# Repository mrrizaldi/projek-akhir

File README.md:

# Proyek Akhir — Sistem Monitoring Detak Jantung Kontinu (IoT Edge Computing)

Monorepo Proyek Akhir untuk pemantauan EKG kontinu dengan klasifikasi aritmia
**di edge**. Sinyal EKG satu lead diakuisisi AD8232, diproses dan diklasifikasi
oleh model TinyML INT8 di ESP32-S3, lalu hasil per detak dipublikasikan lewat
MQTT ke ThingsBoard. Klasifikasi berjalan di alat, bukan di server.

## Struktur

| Subdir | Isi | Toolchain |
|---|---|---|
| `model/` | Jalur TinyML: data MIT-BIH → preprocessing → pelatihan → kuantisasi INT8 → ekspor | Python 3.11 + TensorFlow/TFLite |
| `firmware/` | Program ESP32-S3: akuisisi 360 Hz, deteksi R-peak, inferensi TFLite Micro, MQTT | PlatformIO (C/C++) |
| `dashboard/` | ThingsBoard CE (broker MQTT, rule engine, dashboard) dan skrip pengukuran pipeline | Docker Compose, Python |
| `hardware/` | PCB mainboard rev2: skematik, layout, library DevKitC-1, pemeriksaan otomatis ([`hardware/mainboard/`](hardware/mainboard/README.md)) | KiCad 9 |
| `laporan/` | Dokumen LaTeX: `proposal-pa`, `buku-pa`, `surat-magang`, `shared` | pdflatex + bibtex |
| `scripts/` | Otomasi lintas-komponen (sinkronisasi artefak) | bash |
| `docs/` | Pola penulisan laporan PA dan arsip rencana kerja | Markdown |

## Alur artefak (produsen → konsumen)

- `model/` menghasilkan `model_int8.h` → dikonsumsi `firmware/include/`.
- `model/scripts/export_golden.py` menghasilkan `firmware/test/golden_ref.h`
  (regression test C ↔ Python).
- `model/artifacts/metrics/` (plot eksperimen) dan `dashboard/preview.png`
  menghasilkan figure → dikonsumsi `laporan/*/gambar/`. Diagram ilustrasi
  digambar penulis langsung ke `laporan/*/gambar/`.
- Sinkronisasi lewat `scripts/export_artifacts.sh`. Artefak tidak disalin manual.

Kebijakan commit: figure final dan header `.h` hasil generate **di-commit**,
sehingga laporan dan firmware dapat di-build tanpa menjalankan seluruh pipeline
model. Data mentah MIT-BIH dan berkas intermediate (`.npz`) **di-ignore**
(lihat `.gitignore`).

## Build cepat

```bash
# Laporan (ukuran kertas tetap per projek)
cd laporan/buku-pa && make pdf            # -> output/main.pdf
# Model
cd model && make train && make quantize && make export
# Firmware
cd firmware && pio run -e esp32-s3 -t upload && pio device monitor
cd firmware && pio test -e native         # uji di PC, tanpa board
# Dashboard
cd dashboard && docker compose up -d      # -> http://localhost:8080
```

## Status komponen

| Komponen | Kondisi | Bukti |
|---|---|---|
| `model/` Fase 0-8 | Selesai | `make poc` 8/8, INT8 22,94 KB, DS2 F1 0,6594, AUC 0,9334 |
| `model/` ablasi Fase A-G | Selesai, konfigurasi tidak berubah | 10 usul × 3-6 seed; TEST-B/C 85.812 beat / 39 pasien ([peta](model/docs/README.md)) |
| `firmware/` env `esp32-s3` | Berjalan di board | Inferensi 26,6 ms/detak, tensor arena 12.948 B, sampel hilang 0; MQTT PDSR 99,2-100%, latensi median 939-1.108 ms |
| Akuisisi sinyal tubuh | Selesai: data resmi = sesi 22 Okt 2026 siang (R1–R4, 927,1 s, 4/4 Berhasil) | Indeks sesi di [`model/data/recordings/README.md`](model/data/recordings/README.md); rekaman pengembangan diarsipkan di [`model/data/arsip/rekaman-uji-coba/`](model/data/arsip/rekaman-uji-coba/README.md) |
| `firmware/` test perangkat | Lulus di board | `pio test -e esp32-s3`: 29 test (preprocessing, inferensi, buzzer, TFT, ADC, INA219, tombol, integrasi replay) |
| `firmware/` env `native` | Lulus | `pio test -e native`: 23 test |
| `dashboard/` | Berjalan | ThingsBoard CE self-host, dashboard tujuh widget, uji deduplikasi |
| `laporan/proposal-pa` | Lengkap | Bab 1-3 dan abstrak |
| `laporan/buku-pa` | Draf Bab 1-5 | Gambar ilustrasi berupa placeholder (`grep -rn PLACEHOLDER-GAMBAR laporan/`); angka konsumsi daya menunggu pengukuran (`grep -rn PLACEHOLDER-DATA laporan/buku-pa`) |

Status rinci per fase model berada di `model/CLAUDE.md`. Berkas ini hanya peta,
agar tidak ada dua sumber kebenaran. Pekerjaan yang masih terbuka (konsumsi
daya, WiFi OFF darurat, rekaman ke server, PCB rev2) didaftar bertanggal di
[`model/CLAUDE.md` §Pekerjaan terbuka](model/CLAUDE.md#pekerjaan-terbuka).

## Peta dokumentasi

| Dokumen | Isi |
|---|---|
| [`CLAUDE.md`](CLAUDE.md) | Aturan kerja repo, gate point, kebijakan gambar |
| [`model/README.md`](model/README.md) | Ringkasan komponen model |
| [`model/docs/README.md`](model/docs/README.md) | Peta walkthrough Fase 0-8 dan HW, angka rujukan, eksperimen yang tidak diadopsi |
| [`model/docs/arsip/README.md`](model/docs/arsip/README.md) | Indeks arsip desain, rencana, dan changelog eksperimen model/hardware |
| [`firmware/README.md`](firmware/README.md) | Env PlatformIO, perintah, pin map, perintah serial |
| [`dashboard/README.md`](dashboard/README.md) | ThingsBoard, kontrak payload, pengukuran pipeline |
| [`.claude/skills/`](.claude/skills/) | Skill penulisan laporan (`struktur-pa`, `narasi-pa`, `tabel-pa`, `buku-ikut-proposal`) dan firmware |
| [`docs/arsip/README.md`](docs/arsip/README.md) | Indeks arsip rencana kerja laporan |
| [`scripts/README.md`](scripts/README.md) | Otomasi lintas-komponen (sinkronisasi artefak) |
| [`model/docs/arsip/2026-10-08-pcb-rev2-adjustment.md`](model/docs/arsip/2026-10-08-pcb-rev2-adjustment.md) | Penyesuaian PCB rev1 → rev2 (skematik KiCad di luar repo) |
| `laporan/CLAUDE.md` | Aturan gaya penulisan laporan |
| `model/PRD_Model_Aritmia_TinyML.pdf` | Spesifikasi resmi jalur model |

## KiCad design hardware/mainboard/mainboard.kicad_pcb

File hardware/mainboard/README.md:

# Mainboard (PCB rev2)

Proyek KiCad untuk papan induk alat: ESP32-S3-DevKitC-1 N16R8, AD8232, TFT
ST7789 1,47", INA219, modul buzzer pasif, tiga tombol, dan jalur catu
baterai 18650 (TP4056 + boost MT3608) dengan saklar on-off. Semua modul
dipasang lewat header 2,54 mm. Papan dua lapis, 110 × 103 mm.

Kondisi: skematik dan layout lengkap, pemeriksaan otomatis lulus (lihat
**Pemeriksaan**). Belum difabrikasi, dan butir di **Yang belum terverifikasi**
harus dicek pada modul fisik sebelum Gerber dikirim.

## Berkas

| Berkas | Isi |
|---|---|
| `mainboard.kicad_pro`, `.kicad_sch`, `.kicad_pcb` | proyek KiCad 9.0.2 |
| `lib/PA.kicad_sym`, `lib/PA.pretty/` | simbol dan footprint ESP32-S3-DevKitC-1 (library proyek, dirujuk lewat `${KIPRJMOD}`) |
| `cek_board.py` | pemeriksaan netlist, ERC, DRC, dan paritas skematik–PCB; memanggil `cek_tata_letak.py` |
| `cek_tata_letak.py` | pemeriksaan pcbnew (`/usr/bin/python3`): lebar jalur per netclass, jarak courtyard ≥ 1 mm, teks depan dan belakang |
| `tata_letak.py` | alat layout (`/usr/bin/python3`): posisi terkunci, rute manual, pembersihan sesudah autoroute, pad GND solid, tuang zona, penempat teks, ukiran |

Berkas dibuat dengan KiCad 9.0.2 dan bisa dibuka KiCad 10. Arah sebaliknya
tidak bisa: berkas KiCad 10 (misalnya skematik rev2 yang disusun dengan
KiCad 10.0.6) ditolak KiCad 9 dengan pesan `Failed to load schematic`.

## Peta pin

Sama dengan `firmware/include/perangkat.h`. Nomor pad U1 mengikuti footprint
resmi Espressif: pad 1–22 kolom kiri dari atas (3V3 … GND), pad 23–44 kolom
kanan dari bawah (GND … GND). Urutan fisik kedua kolom sudah dicocokkan 44/44
dengan gambar pinout resmi ESP32-S3-DevKitC-1.

| Fungsi | GPIO | Pad U1 | Net | Tujuan |
|---|---|---|---|---|
| EKG OUT / LO− / LO+ | 1 / 2 / 42 | 41 / 40 / 39 | `ECG_OUT` / `ECG_LON` / `ECG_LOP` | J3 pin 3 / 4 / 5 |
| TFT SCK / MOSI | 9 / 8 | 15 / 12 | `TFT_SCK` / `TFT_MOSI` | J2 pin 3 / 4 |
| TFT RES / DC | 10 / 11 | 16 / 17 | `TFT_RST` / `TFT_DC` | J2 pin 5 / 6 |
| Buzzer | 13 | 19 | `BUZZ` | J9 pin 2 |
| Tombol 1 / 2 / 3 | 4 / 5 / 6 | 4 / 5 / 6 | `BTN1..3` | SW1..3 ke GND |
| INA219 SDA / SCL | 17 / 18 | 10 / 11 | `I2C_SDA` / `I2C_SCL` | U2 pin 4 / 3 |
| 3V3 | – | 1, 2 | `+3V3` | semua VCC modul, SDN AD8232, BLK TFT |
| 5V | – | 21 | `+5V` | keluaran D2 |
| GND | – | 22, 23, 24, 44 | `GND` | semua pin GND DevKit tersambung |

Urutan pin header modul:

| Ref | Modul | Pin 1 → n |
|---|---|---|
| J3 | AD8232 | GND, 3V3, OUT, LO−, LO+, SDN |
| J2 | TFT ST7789 | GND, VCC, SCL, SDA, RES, DC, CS, BLK (CS ke GND, BLK ke 3V3) |
| U2 | INA219 | VCC, GND, SCL, SDA, VIN−, VIN+ |
| J9 | buzzer A18009 | GND, I/O, VCC |
| J1 | boost MT3608 | VIN+, VIN−, VOUT+, VOUT− |
| J10 | saklar on-off berlampu (di casing) | masuk (VSYS), keluar ke boost (VSW), GND lampu |
| J4 / J5 / J6 | TP4056 | IN+ IN− / B+ B− / OUT+ OUT− |
| J8 | kabel holder 18650 (JST PH) | +, − |

## Catu daya

```
 J8 baterai ── J5 B+/B− (TP4056) ── J6 OUT+ = VBAT_OUT ── U2 VIN+ ─shunt─ VIN− = VBAT_SENSE
                                                                             │
                     J4 IN+ = VCHG ──┬── gate Q1 (R1 10k ke GND)             D
                                     │                                   Q1 AO3401A
                                     └── D1 SS34 ──► VSYS ◄──────────────── S
                                                      │
                                              J10 saklar on-off
                                                      │ VSW
                                     J1 VIN+ ◄────────┘    J1 VOUT+ = VBOOST ── D2 SS34 ──► +5V ── U1 pin 5V, C1 47 µF, C2 100 nF
```

- Tanpa charger: gate Q1 ditarik R1 ke GND, Q1 menyala, baterai mencatu boost.
- Dengan charger: VCHG 5 V mematikan Q1, sehingga baterai hanya menerima arus
  isi dari TP4056 dan tidak mencatu beban. Boost dicatu dari VCHG lewat D1.
  Katoda D1 ada di VSYS (masukan boost), bukan di +5V. Kalau katoda D1 di +5V,
  body diode Q1 tetap mengalirkan baterai ke boost dan sel terkuras selama
  dicas.
- Saklar J10 memutus VSYS sebelum boost. OFF berarti alat mati total, juga
  saat charger tercolok, sedangkan pengisian baterai tetap berjalan karena
  TP4056 ada di depan saklar. Lampu saklar dicatu dari VSYS (±3,0–4,6 V).
- R2 1 MΩ (R_Dummy di skematik rev2) dipertahankan apa adanya: beban ±4 µA
  dari VBAT_SENSE ke GND.

## Layout

| Area | Isi | Alasan |
|---|---|---|
| Tengah | U1, USB menghadap tepi bawah | semua GPIO terpakai ada di kolom kiri kecuali EKG |
| Kanan atas | J3 AD8232, C4 | pad 39–41 U1 sejajar J3 pin 3–5, jalur EKG lurus 9 mm |
| Kanan bawah | jalur baterai, INA219, Q1, D1, D2, header TP4056/boost/baterai | jauh dari AD8232; modul boost di luar papan lewat kabel |
| Kiri | TFT, buzzer; tombol SW1–SW3 berjajar tegak di tepi kiri (x 53–57,5, y 57,5–88) | SPI TFT berlawanan sisi dengan jalur analog; tombol mudah dijangkau dari sisi papan |
| Atas U1 | rule area `antena_devkit` | tanpa tembaga dan via di bawah antena WROOM |
| Bawah | rule area `holder_18650` 80 × 24 mm (x 66–146, y 116,5–140,5) + garis silkscreen | tempat holder 18650 berkabel yang ditempel; baterai 65 × 18 mm, holder ±77 × 21 mm, margin 1,5 mm tiap sisi; footprint dilarang, jalur dan GND pour boleh |

Jalur yang dirute manual dan dikunci (`locked`): tiga jalur EKG (F.Cu),
catu AD8232 (3V3 dari pad 2 U1 lewat B.Cu ke C4/J3 pin 2, SDN ke 3V3),
I2C ke INA219 (SDA di F.Cu; SCL turun lewat via ke B.Cu di x 118 dan
menyeberang di bawah SDA, karena urutan pin INA219 SCL–SDA terbalik terhadap
urutan dari DevKit), 3V3 ke INA219, 3V3 sisi kiri (U1 pad 2 ke C3), dan
seluruh jalur daya (termasuk cabang gate Q1 dan R2). Gate Q1 lewat B.Cu
karena urutan pin SOT-23 (G, D, S searah jarum jam) berlawanan dengan arah
net di sekitarnya, dan gate tidak membawa arus. Sisa sinyal digital dirute
Freerouting 2.3.0. GND dituang di kedua lapis.

Batas JLCPCB untuk 2 lapis 1 oz (halaman *PCB Capabilities*): jalur/clearance
0,10 mm, jalur ke lubang PTH 0,28 mm (rekomendasi 0,35 mm), via lubang 0,15 /
pad 0,25 mm (lubang < 0,3 mm lebih mahal), ring PTH 0,18 mm (rekomendasi
0,25 mm), teks silkscreen tinggi 1,0 mm dan garis 0,15 mm, tembaga ke tepi
0,2 mm. Profil papan ini adalah profil "ideal teknis": lebar mengikuti
kebutuhan arus menurut IPC-2221 (1 oz, kenaikan suhu 10 °C: 0,3 mm ±1 A,
1,0 mm ±2,4 A), jarak dan ring mengikuti rekomendasi JLCPCB.

| Netclass (`mainboard.kicad_pro`) | Net | Lebar | Clearance | Via |
|---|---|---|---|---|
| `Default` | sinyal digital, `+3V3`, GND | 0,3 mm | 0,35 mm | 0,9/0,4 mm |
| `ECG` | `/ECG_*` | 0,4 mm | 0,35 mm | 0,9/0,4 mm |
| `Power` | `/+5V /VBOOST /VSYS /VSW /VCHG /VBAT_OUT /VBAT_SENSE /BAT+ /BAT-` | 1,0 mm | 0,35 mm | 1,2/0,6 mm |

Arus terbesar di papan: jalur baterai/boost ±1 A puncak (MT3608 dibatasi
2 A), sehingga 1,0 mm memberi margin di atas batas boost. Sinyal hanya
membawa miliampere; 0,3 mm dipilih karena tiga kali minimum JLCPCB dan muat di
sela pin DevKit tanpa menyempit (0,3 + 2 × 0,35 = 1,0 mm ≤ celah 1,04 mm).

Jarak antar-courtyard komponen minimal 1,0 mm. Semua pad GND memakai thermal
relief kecuali C2-2, yang disambung penuh (*solid*) karena hanya mendapat satu
spoke di sela antara U1 dan jalur +5V.

Teks: referensi di silkscreen (tinggi ≥ 1,0 mm, batas JLCPCB) dan value di
Fab, sejajar sumbu header dan di sisi yang berlawanan, tanpa menumpuk dan
tidak di atas pad. Pengecualian: ref C4 mendatar di atas C4, karena celah
9 mm antara U1 dan J3 tidak muat teks tegak.

## Perbedaan terhadap skematik rev2

Skematik rev2 (`mainboard.kicad_sch`, KiCad 10.0.6, PCB belum di-layout)
dipakai sebagai acuan rangkaian. Perbedaannya:

| Bagian | Rev2 | Mainboard ini | Alasan |
|---|---|---|---|
| Net 3V3 | label `3.3V` (ESP, AD8232, buzzer) dan simbol `+3.3V` (TFT) | satu net `+3V3` | nama berbeda di KiCad = dua net terpisah; VCC TFT tidak tersambung ke 3V3 ESP |
| Pull-up tombol | R11–R13 1 kΩ ke +5V | dihapus, `INPUT_PULLUP` | GPIO ESP32-S3 maksimum 3,6 V |
| BLK TFT | tidak tersambung | ke 3V3 | backlight selalu menyala |
| Katoda D1 | ke +5V | ke VSYS | baterai tidak terkuras saat dicas |
| Saklar daya | tidak ada | J10 di VSYS | |
| Simbol U1 | ESP32-S3-DEVKITC-1-N8R8 | ESP32-S3-DevKitC-1-N16R8 | papan yang dipakai N16R8 |
| GND DevKit | hanya pin GND kanan atas | keempat pin GND | |
| Header boost | 2 pin (Input, Output) | 4 pin dengan GND | GND modul boost punya jalur sendiri |
| Footprint header J1–J9 | belum diisi | PinSocket/PinHeader 2,54 mm, JST PH untuk baterai | |
| Nama net | `SCL`, `OUT`, `buzz`, dll. | berprefiks (`I2C_`, `TFT_`, `ECG_`) | nama sama otomatis menyatu di KiCad |

Ukuran footprint pasif mengikuti rev2: R dan C 0805 HandSolder, tombol
`SW_PUSH_6mm_H7.3mm`. C1 memakai `CP_Radial_D5.0mm_P2.00mm` (pad sama dengan
rev2) agar tanda polaritas tercetak.

## Footprint ESP32-S3-DevKitC-1

Diambil dari library resmi Espressif (`espressif/kicad-libraries`,
`ESP32-S3-DevKitC.kicad_mod` dan simbol `ESP32-S3-DevKitC`). Posisi pad tidak
diubah: 2 × 22 pin, pitch 2,54 mm, jarak antar-baris 22,86 mm. Yang diubah
hanya lubang dan pad: lubang 0,8 mm menjadi 1,0 mm, pad oval 2,0 mm (mendatar)
× 1,5 mm (tegak), ring 0,25 mm sesuai rekomendasi JLCPCB. Pin header persegi
0,64 mm berdiagonal 0,9 mm, sehingga tidak masuk lubang 0,8 mm; 1,0 mm sama
dengan footprint `PinSocket` KiCad. Pad 1,5 mm tegak menyisakan celah 1,04 mm
antar-pin satu kolom, cukup untuk jalur 0,3 mm + clearance 2 × 0,35 mm. Jalur
3V3 ke AD8232 dan I2C ke INA219 menyeberangi kolom pin lewat celah ini. Simbol diturunkan dari format KiCad 10
ke format KiCad 9 tanpa mengubah pin.

## Pemeriksaan

```bash
python3 hardware/mainboard/cek_board.py
```

Hasil yang diharapkan:

```
netlist: 87/87 pin sesuai peta
+5V di luar jalur daya: tidak ada
ERC: error 0 warning 0
DRC error: 0, unconnected: 0, paritas skematik: 0
lebar jalur: 0 temuan
jarak courtyard: 0 temuan
teks: 0 temuan
LULUS
```

Skrip keluar dengan kode 1 bila satu pin saja menyimpang dari peta di atas,
bila ada jalur lebih tipis dari netclass-nya, dua courtyard berjarak < 1 mm,
atau teks menumpuk, di atas pad, keluar tepi, atau tidak searah header.
Peta pin di skrip (`PIN_U1`, `PIN_LAIN`) wajib diperbarui bersamaan dengan
`perangkat.h` setiap kali pin dipindah.

## Ukiran nama

Silkscreen sisi belakang, dicerminkan agar terbaca dari bawah, di balik area
holder (yang bebas footprint sehingga sisi belakangnya tanpa pad):

| Baris | Teks | Tinggi | Posisi |
|---|---|---|---|
| 1 | Muhammad Rafi Rizaldi | 2,5 mm | (106; 125) |
| 2 | 3123600001 | 2,0 mm | (106; 131) |

Teksnya diatur di `UKIRAN` dan `POSISI_UKIRAN` (`tata_letak.py`).

## Mengubah desain

Perubahan rangkaian:

1. Buka `mainboard.kicad_pro` di KiCad 9 atau lebih baru.
2. Ubah skematik. Penerapan ke board lewat skrip pcbnew (lihat skill
   `kicad-pcb-pa` aturan 5), bukan F8, agar nama net tetap `/NAMA`.

Rute ulang seluruh papan (posisi di `POSISI`, rute manual di fungsi `rute_*`
pada `tata_letak.py`), dijalankan dari `hardware/mainboard/`:

```bash
/usr/bin/python3 tata_letak.py hapus
/usr/bin/python3 tata_letak.py rute
/usr/bin/python3 tata_letak.py tuang
```

Lalu autoroute sisa sinyal dengan Freerouting (server MCP kicad: `open_project`,
`autoroute` dengan `maxPasses` 60), kemudian:

```bash
/usr/bin/python3 tata_letak.py bersih
/usr/bin/python3 tata_letak.py solid
/usr/bin/python3 tata_letak.py teks
/usr/bin/python3 tata_letak.py ukiran
/usr/bin/python3 tata_letak.py tuang
python3 cek_board.py
```

Hasil yang diharapkan: baris terakhir `cek_board.py` adalah `LULUS`.
Freerouting bisa melapor sukses sambil meninggalkan sambungan; bila DRC
melapor `unconnected`, sambungan itu ditambahkan ke fungsi `rute_*` di
`tata_letak.py` lalu seluruh urutan diulang dari `hapus`.

## Yang belum terverifikasi

1. **Jarak antar-baris header DevKit fisik.** Footprint memakai 22,86 mm
   (resmi Espressif). Ukur papan N16R8 yang dipakai, karena klon bisa berbeda.
2. **Urutan pin tiap modul** (J2, J3, U2, J9) terhadap silkscreen modul yang
   dipegang. Urutan pin TFT 1,47" berbeda antar-vendor.
3. **Ruang mekanik modul.** Ukuran dari penjual saling berbeda (AD8232 35×22
   sampai 36×33 mm, TFT 19,5×44,5 atau 22×38,5 mm, INA219 22×20 mm), dan
   outline badan modul belum digambar di PCB. Bila dibaringkan ke arah dalam
   papan, badan TFT menutupi C6 dan badan AD8232 menutupi H2. Komponen SMD di
   bawahnya aman selama modul terangkat di atas female header. Kepala baut H2
   perlu dicek terhadap sisi bawah modul AD8232.
4. **Jalur catu dengan D1 di VSYS** belum diuji di breadboard. Ukur VSYS dan
   +5V dengan charger tercolok dan tercabut, dan pastikan arus baterai ≈ 0
   saat dicas.
5. **Konektor baterai** memakai JST PH 2 mm. Sesuaikan dengan kabel holder
   18650 yang dipakai, dan ukur holdernya: area di papan 80 × 24 mm.
6. **Tegangan lampu saklar J10.** Lampu dicatu VSYS ±3,0–4,6 V. Lampu LED
   12 V atau neon 220 V tidak akan menyala di tegangan ini; cek tulisan di
   badan saklar sebelum memakai pin lampu.

## Ekspor fabrikasi

Berkas untuk JLCPCB dibuat dengan pengaturan dari panduan resmi JLCPCB untuk
KiCad: lapisan F/B.Cu, F/B.Paste, F/B.Silkscreen, F/B.Mask, Edge.Cuts, ekstensi
Protel, silkscreen dikurangi mask, via di-*tent* (setelan papan
`(tenting front back)`), zona dituang sebelum plot, drill Excellon mm desimal
origin absolut dengan PTH dan NPTH terpisah plus peta drill.

```bash
hardware/mainboard/ekspor_fab.sh
```

Hasil: `hardware/mainboard/fab/mainboard-gerber-jlcpcb.zip` (14 berkas di akar
zip), yang di-upload di tombol *Add gerber file*. Folder `fab/` tidak
di-commit karena dibuat ulang oleh perintah di atas.

Pemeriksaan isi zip terhadap papan (Kondisi uji: 18 Okt 2026):

| Yang dicek | Gerber/drill | Papan |
|---|---|---|
| Lubang PTH | 101 (0,4 ×3, 0,6 ×2, 0,75 ×2, 0,8 ×2, 1,0 ×80, 1,1 ×12) | sama |
| Lubang NPTH | 4 × 3,2 mm | sama |
| Flash F.Cu / B.Cu | 122 / 101 | 117 pad + 5 via / 96 pad THT + 5 via |
| Bukaan mask depan | 121 tanpa via | 117 pad + 4 lubang baut (via ter-*tent*) |
| Pad paste depan / belakang | 21 / 0 | 21 pad SMD / 0 |
| Garis potong | 110,0 × 103,0 mm | sama |

Tampilan visual Gerber dicek di pratinjau JLCPCB setelah upload dan, bila
memilih *Confirm Production File*, di berkas produksi yang dikirim engineer.

Butir di **Yang belum terverifikasi** dicek sebelum zip di-upload.

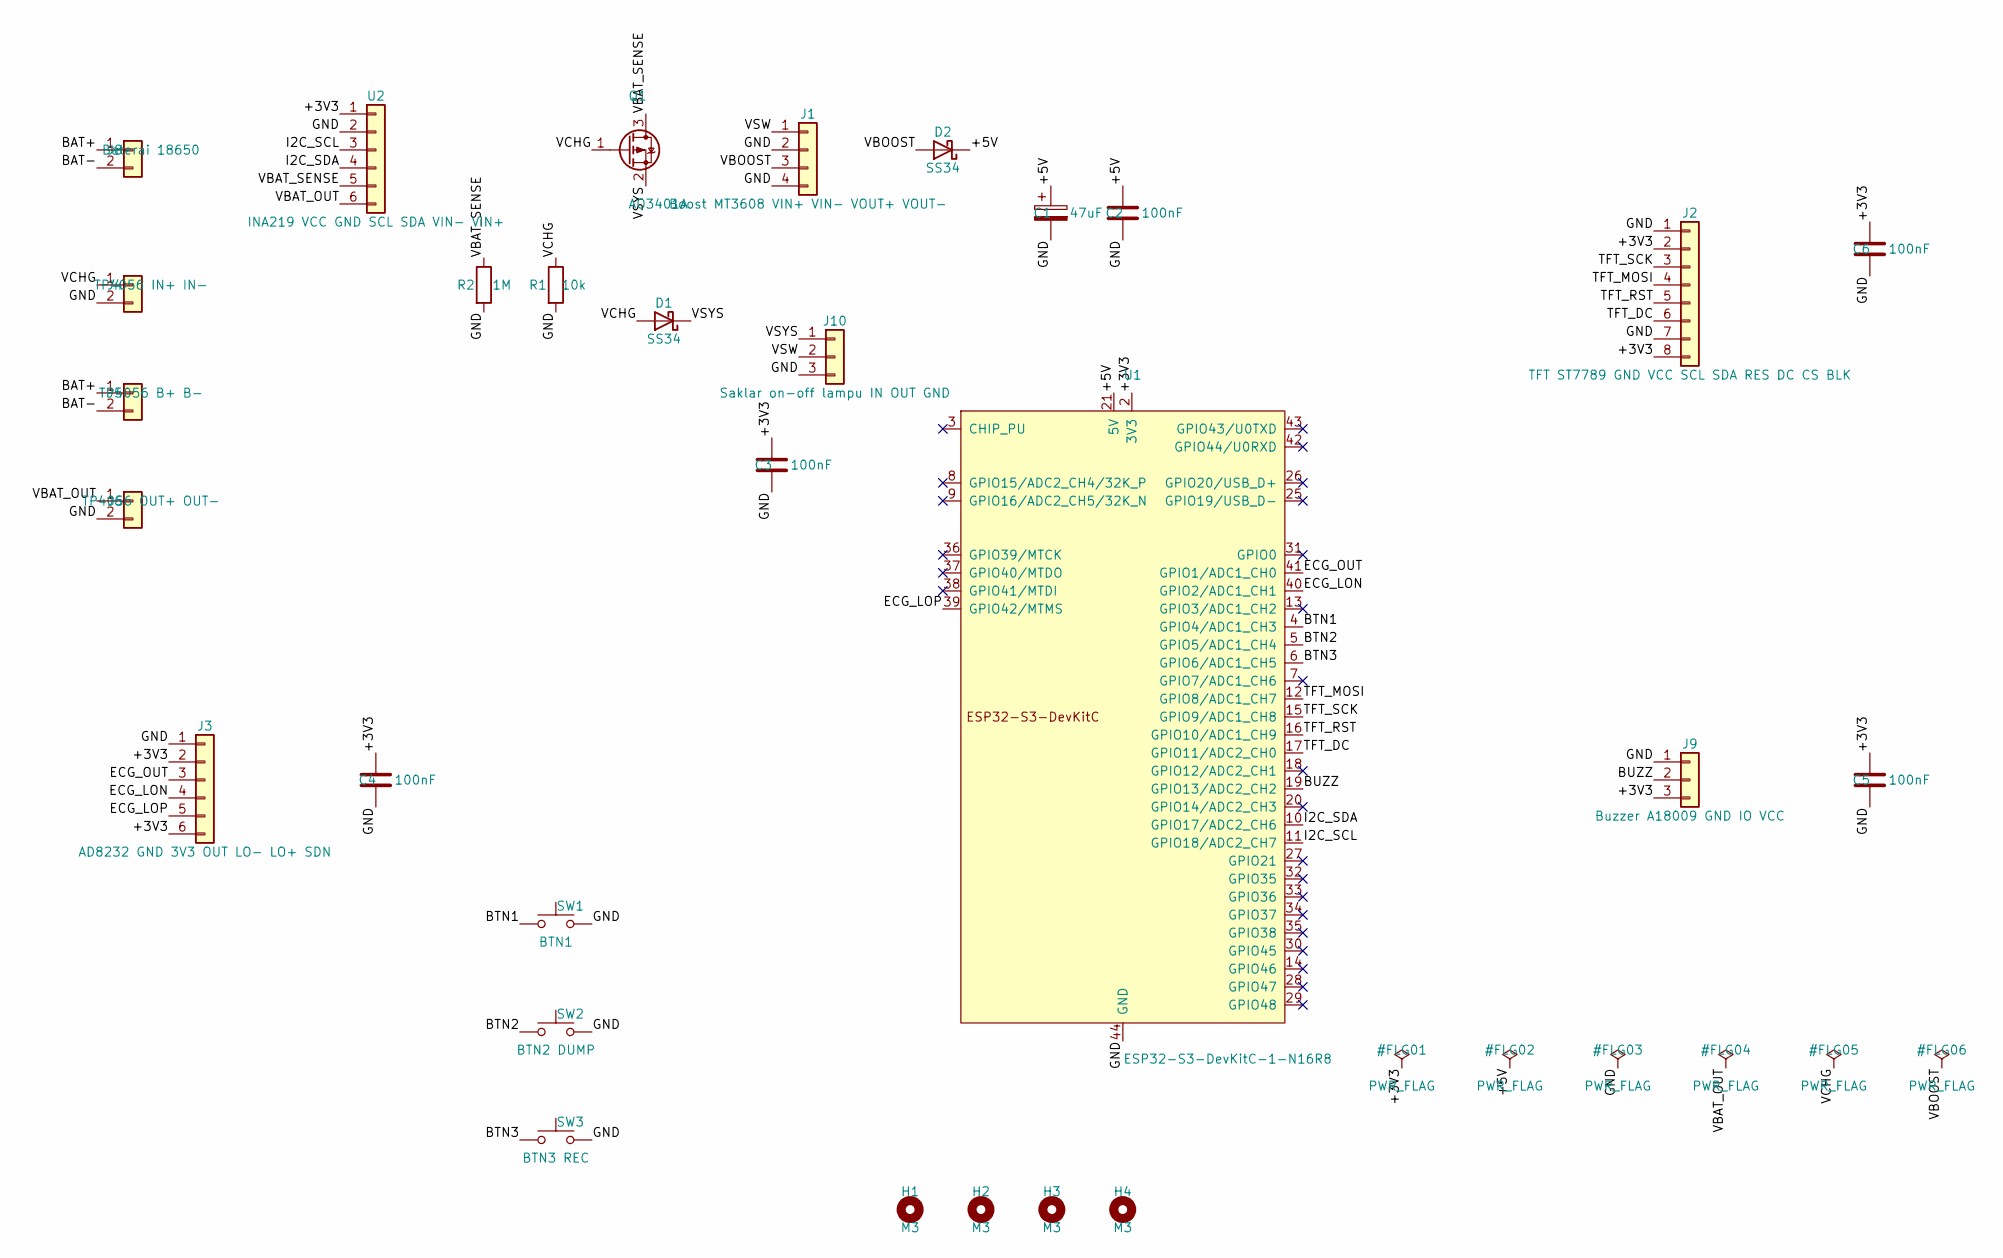
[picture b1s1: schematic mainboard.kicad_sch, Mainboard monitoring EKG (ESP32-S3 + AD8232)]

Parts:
C1: 47uF; CP_Radial_D5.0mm_P2.00mm
C2, C3, C4, C5, C6: 100nF; C_0805_2012Metric_Pad1.18x1.45mm_HandSolder
D1, D2: SS34; D_SMA
H1, H2, H3, H4: M3; MountingHole_3.2mm_M3
J1: Boost MT3608 VIN+ VIN- VOUT+ VOUT-; PinHeader_1x04_P2.54mm_Vertical
J2: TFT ST7789 GND VCC SCL SDA RES DC CS BLK; PinSocket_1x08_P2.54mm_Vertical
J3: AD8232 GND 3V3 OUT LO- LO+ SDN; PinSocket_1x06_P2.54mm_Vertical
J4: TP4056 IN+ IN-; PinHeader_1x02_P2.54mm_Vertical
J5: TP4056 B+ B-; PinHeader_1x02_P2.54mm_Vertical
J6: TP4056 OUT+ OUT-; PinHeader_1x02_P2.54mm_Vertical
J8: Baterai 18650; JST_PH_B2B-PH-K_1x02_P2.00mm_Vertical
J9: Buzzer A18009 GND IO VCC; PinSocket_1x03_P2.54mm_Vertical
J10: Saklar on-off lampu IN OUT GND; PinHeader_1x03_P2.54mm_Vertical
Q1: AO3401A; SOT-23
R1: 10k; R_0805_2012Metric_Pad1.20x1.40mm_HandSolder
R2: 1M; R_0805_2012Metric_Pad1.20x1.40mm_HandSolder
SW1: BTN1; SW_PUSH_6mm_H7.3mm
SW2: BTN2 DUMP; SW_PUSH_6mm_H7.3mm
SW3: BTN3 REC; SW_PUSH_6mm_H7.3mm
U1: ESP32-S3-DevKitC-1-N16R8; ESP32-S3-DevKitC-1
U2: INA219 VCC GND SCL SDA VIN- VIN+; PinSocket_1x06_P2.54mm_Vertical

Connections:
/+3V3: C3.1, C4.1, C5.1, C6.1, J2.2, J2.8, J3.2, J3.6, J9.3, U1.1 (3V3), U1.2 (3V3), U2.1
/+5V: C1.1, C2.1, D2.1 (K), U1.21 (5V)
/BAT+: J5.1, J8.1
/BAT-: J5.2, J8.2
/BTN1: SW1.1, U1.4 (GPIO4/ADC1_CH3)
/BTN2: SW2.1, U1.5 (GPIO5/ADC1_CH4)
/BTN3: SW3.1, U1.6 (GPIO6/ADC1_CH5)
/BUZZ: J9.2, U1.19 (GPIO13/ADC2_CH2)
/ECG_LON: J3.4, U1.40 (GPIO2/ADC1_CH1)
/ECG_LOP: J3.5, U1.39 (GPIO42/MTMS)
/ECG_OUT: J3.3, U1.41 (GPIO1/ADC1_CH0)
/GND: C1.2, C2.2, C3.2, C4.2, C5.2, C6.2, J1.2, J1.4, J2.1, J2.7, J3.1, J4.2, J6.2, J9.1, J10.3, R1.2, R2.2, SW1.2, SW2.2, SW3.2, U1.22 (GND), U1.23 (GND), U1.24 (GND), U1.44 (GND), U2.2
/I2C_SCL: U1.11 (GPIO18/ADC2_CH7), U2.3
/I2C_SDA: U1.10 (GPIO17/ADC2_CH6), U2.4
/TFT_DC: J2.6, U1.17 (GPIO11/ADC2_CH0)
/TFT_MOSI: J2.4, U1.12 (GPIO8/ADC1_CH7)
/TFT_RST: J2.5, U1.16 (GPIO10/ADC1_CH9)
/TFT_SCK: J2.3, U1.15 (GPIO9/ADC1_CH8)
/VBAT_OUT: J6.1, U2.6
/VBAT_SENSE: Q1.3 (D), R2.1, U2.5
/VBOOST: D2.2 (A), J1.3
/VCHG: D1.2 (A), J4.1, Q1.1 (G), R1.1
/VSW: J1.1, J10.2
/VSYS: D1.1 (K), J10.1, Q1.2 (S)

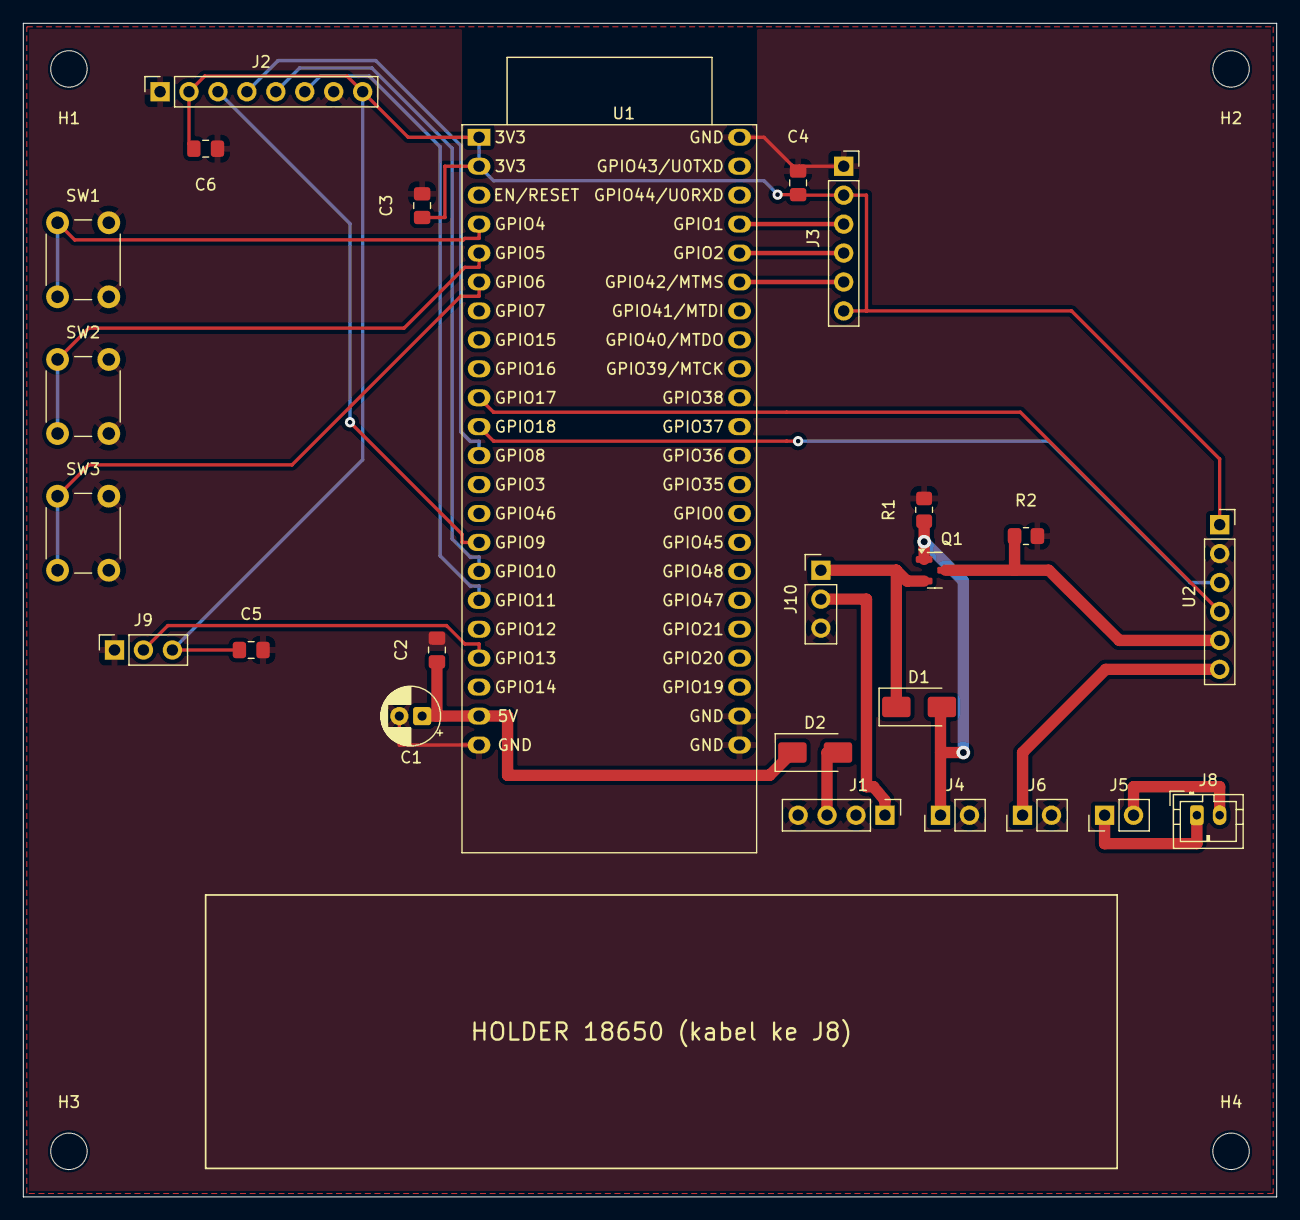
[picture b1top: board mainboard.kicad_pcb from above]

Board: 2 copper layers, 110.0 x 103.0 mm, 29 parts (0 on the bottom side), 24 nets.

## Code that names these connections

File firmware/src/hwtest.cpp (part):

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// Pin map PCB rev1 (schematic_rev_1.pdf). TFT CS diikat ke GND.
constexpr adc1_channel_t KANAL_EKG = ADC1_CHANNEL_0; // GPIO 1
constexpr int PIN_LON = 2, PIN_LOP = 42;
constexpr int TFT_SCK = 9, TFT_MOSI = 8, TFT_RST = 10, TFT_DC = 11;
// Modul buzzer 3 pin (VCC, GND, I/O) berisi transistor: I/O LOW = BUNYI,
// HIGH = diam (deskripsi produk A07009/A18009). Jadi diam = HIGH, bukan LOW.
// BUZZER_PASIF=1 (A18009): gelombang kotak LEDC, keluarannya dibalik.
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#ifndef BUZZER_PASIF
#define BUZZER_PASIF 1
#endif
constexpr int PIN_BUZZ = 13, KANAL_BUZZ = 0;
// Knob: buzzer pasif paling keras di frekuensi resonansinya, beda per part.
// Cari dengan '[' / ']' di serial, lalu kunci angkanya di sini.
static uint32_t nada_hz = 2000;
constexpr uint32_t BIP_MS = 50;
constexpr int PIN_BTN[3] = {4, 5, 6};     // ke GND, pull-up internal.
constexpr int I2C_SDA = 17, I2C_SCL = 18; // INA219, VCC modul WAJIB 3V3
// Knob kalibrasi: koreksi kalau multimeter tidak setuju,
// R_baru = R_lama x (I_ina219 / I_multimeter).
constexpr float R_SHUNT = 0.1f;
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// Diam DULU: modul aktif-LOW, pin yang belum di-set bisa berarti bunyi.
static void pasang_buzzer()
{
    pinMode(PIN_BUZZ, OUTPUT);
    digitalWrite(PIN_BUZZ, HIGH);
#if BUZZER_PASIF
    ledcSetup(KANAL_BUZZ, nada_hz, 8);
    ledc_channel_config_t ch = {};
    ch.gpio_num = PIN_BUZZ;
    ch.speed_mode = LEDC_LOW_SPEED_MODE;
    ch.channel = (ledc_channel_t)KANAL_BUZZ;
    ch.timer_sel = LEDC_TIMER_0; // kanal 0 -> timer 0, sama dengan ledcSetup
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static void diag_fase()
{
    static const char *const NAMA[4] = {"1 HIGH=diam", "2 LOW (DC) ", "3 PWM 2kHz ", "4 LEPAS    "};
    ledcDetachPin(PIN_BUZZ);
    if (diag == 0)
    {
        pinMode(PIN_BUZZ, OUTPUT);
        digitalWrite(PIN_BUZZ, HIGH);
    }
    if (diag == 1)
    {
        pinMode(PIN_BUZZ, OUTPUT);
        digitalWrite(PIN_BUZZ, LOW);
    }
    if (diag == 2)
    {
        ledcSetup(KANAL_BUZZ, 2000, 8);
        ledcAttachPin(PIN_BUZZ, KANAL_BUZZ);
        ledcWrite(KANAL_BUZZ, 128);
    }
    if (diag == 3)
        pinMode(PIN_BUZZ, INPUT);
    tft.fillRect(0, GY, W, GH, ST77XX_BLACK);
    tft.setTextSize(3);
    tft.setTextColor(ST77XX_YELLOW, ST77XX_BLACK);
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#if BUZZER_PASIF
    ledcWriteTone(KANAL_BUZZ, nyala ? nada_hz : 0); // duty 0 + invert = HIGH = diam
#else
    digitalWrite(PIN_BUZZ, nyala ? LOW : HIGH);
#endif
}

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    timerAlarmEnable(timer);

    bunyi(100);
    Serial.printf("\n=== HWTEST PCB rev1 === fs=%u Hz | EKG GPIO1, LO+ 42, LO- 2, buzzer %s %d @%u Hz, tombol 4/5/6\n",
                  ECG_FS, BUZZER_PASIF ? "pasif" : "aktif", PIN_BUZZ, (unsigned)nada_hz);
    Serial.printf("sumber: %s | 'y' ganti sumber, '+'/'-' BPM dummy, '['/']' nada, 'r' rekam, 'd' dump, 's' status, 'a' alir mentah, 'g' diagnosa buzzer | layar+bip tertunda %u ms dari R | deteksi tiap %u ms\n",
                  nama_sumber(),
                  (unsigned)(TUNDA_BIP * 1000 / ECG_FS), (unsigned)(ECG_LIVE_TIAP * 1000 / ECG_FS));
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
